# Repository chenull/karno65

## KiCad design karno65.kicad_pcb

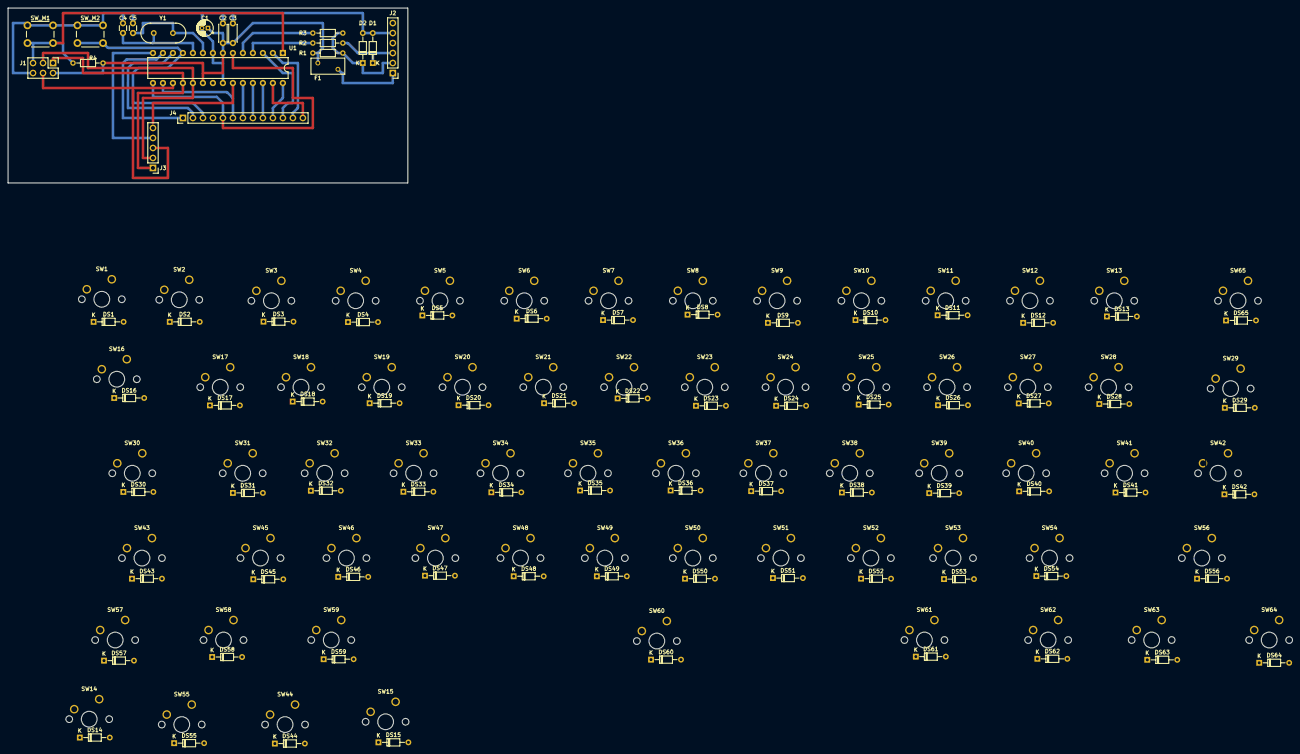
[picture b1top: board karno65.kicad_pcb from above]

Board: 2 copper layers, 101.6 x 44.5 mm, 156 parts (0 on the bottom side), 93 nets.

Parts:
C1: 10u; CP_Radial_D4.0mm_P1.50mm
C2, C3: 100n; C_Disc_D4.3mm_W1.9mm_P5.00mm
C4, C5: 20p; C_Disc_D3.0mm_W1.6mm_P2.50mm
D1, D2: 3.6V; D_DO-34_SOD68_P7.62mm_Horizontal
DS1, DS2, DS3, DS4, DS5, DS6, DS7, DS8, DS9, DS10, DS11, DS12, DS13, DS14, DS15, DS16, DS17, DS18, DS19, DS20, DS21, DS22, DS23, DS24, DS25, DS26, DS27, DS28, DS29, DS30, DS31, DS32, DS33, DS34, DS35, DS36, DS37, DS38, DS39, DS40, DS41, DS42, DS43, DS44, DS45, DS46, DS47, DS48, DS49, DS50, DS51, DS52, DS53, DS54, DS55, DS56, DS57, DS58, DS59, DS60, DS61, DS62, DS63, DS64, DS65: 1N4148; D_DO-34_SOD68_P7.62mm_Horizontal
F1: 100mA; Fuse_BelFuse_0ZRE0005FF_L8.3mm_W3.8mm
J1: AVR_ISP_6; PinHeader_2x03_P2.54mm_Vertical
J2: USB_OTG; PinHeader_1x06_P2.54mm_Vertical
J3: ROWS; PinHeader_1x05_P2.54mm_Vertical
J4: COLS; PinHeader_1x13_P2.54mm_Vertical
R1: 1.5k; R_Axial_DIN0204_L3.6mm_D1.6mm_P7.62mm_Horizontal
R2, R3: 75R; R_Axial_DIN0204_L3.6mm_D1.6mm_P7.62mm_Horizontal
R4: 10k; R_Axial_DIN0204_L3.6mm_D1.6mm_P7.62mm_Horizontal
STAB1, STAB2, STAB3, STAB4, STAB5, STAB6: 2U; MX_Stabilizer_Cutout-2u
SW1: GRV; SW_Cherry_MX1A_1.00u_PCB
SW2: 1; SW_Cherry_MX1A_1.00u_PCB
SW3: 2; SW_Cherry_MX1A_1.00u_PCB
SW4: 3; SW_Cherry_MX1A_1.00u_PCB
SW5: 4; SW_Cherry_MX1A_1.00u_PCB
SW6: 5; SW_Cherry_MX1A_1.00u_PCB
SW7: 6; SW_Cherry_MX1A_1.00u_PCB
SW8: 7; SW_Cherry_MX1A_1.00u_PCB
SW9: 8; SW_Cherry_MX1A_1.00u_PCB
SW10: 9; SW_Cherry_MX1A_1.00u_PCB
SW11: 0; SW_Cherry_MX1A_1.00u_PCB
SW12: MINS; SW_Cherry_MX1A_1.00u_PCB
SW13: EQL; SW_Cherry_MX1A_1.00u_PCB
SW14, SW15, SW44, SW55: SW_Push; SW_Cherry_MX1A_1.00u_PCB
SW16: TAB; SW_Cherry_MX1A_1.50u_PCB
SW17: Q; SW_Cherry_MX1A_1.00u_PCB
SW18: W; SW_Cherry_MX1A_1.00u_PCB
SW19: E; SW_Cherry_MX1A_1.00u_PCB
SW20: R; SW_Cherry_MX1A_1.00u_PCB
SW21: T; SW_Cherry_MX1A_1.00u_PCB
SW22: Y; SW_Cherry_MX1A_1.00u_PCB
SW23: U; SW_Cherry_MX1A_1.00u_PCB
SW24: I; SW_Cherry_MX1A_1.00u_PCB
SW25: O; SW_Cherry_MX1A_1.00u_PCB
SW26: P; SW_Cherry_MX1A_1.00u_PCB
SW27: LBRC; SW_Cherry_MX1A_1.00u_PCB
SW28: RBRC; SW_Cherry_MX1A_1.00u_PCB
SW29: BSLS; SW_Cherry_MX1A_1.50u_PCB
SW30: CAPS; SW_Cherry_MX1A_1.75u_PCB
SW31: A; SW_Cherry_MX1A_1.00u_PCB
SW32: S; SW_Cherry_MX1A_1.00u_PCB
SW33: D; SW_Cherry_MX1A_1.00u_PCB
SW34: F; SW_Cherry_MX1A_1.00u_PCB
SW35: G; SW_Cherry_MX1A_1.00u_PCB
SW36: H; SW_Cherry_MX1A_1.00u_PCB
SW37: J; SW_Cherry_MX1A_1.00u_PCB
SW38: K; SW_Cherry_MX1A_1.00u_PCB
SW39: L; SW_Cherry_MX1A_1.00u_PCB
SW40: SCLN; SW_Cherry_MX1A_1.00u_PCB
SW41: QUOT; SW_Cherry_MX1A_1.00u_PCB
SW42: ENT; SW_Cherry_MX1A_1.00u_PCB
SW43: LSFT; SW_Cherry_MX1A_1.00u_PCB
SW45: Z; SW_Cherry_MX1A_1.00u_PCB
SW46: X; SW_Cherry_MX1A_1.00u_PCB
SW47: C; SW_Cherry_MX1A_1.00u_PCB
SW48: V; SW_Cherry_MX1A_1.00u_PCB
SW49: B; SW_Cherry_MX1A_1.00u_PCB
SW50: N; SW_Cherry_MX1A_1.00u_PCB
SW51: M; SW_Cherry_MX1A_1.00u_PCB
SW52: COMM; SW_Cherry_MX1A_1.00u_PCB
SW53: DOT; SW_Cherry_MX1A_1.00u_PCB
SW54: SLSH; SW_Cherry_MX1A_1.00u_PCB
SW56: RSFT; SW_Cherry_MX1A_1.00u_PCB
SW57: LCTL; SW_Cherry_MX1A_1.25u_PCB
SW58: LGUI; SW_Cherry_MX1A_1.25u_PCB
SW59: LALT; SW_Cherry_MX1A_1.25u_PCB
SW60: SPC; SW_Cherry_MX1A_1.00u_PCB
SW61: RALT; SW_Cherry_MX1A_1.25u_PCB
SW62: RGUI; SW_Cherry_MX1A_1.25u_PCB
SW63: APP; SW_Cherry_MX1A_1.25u_PCB
SW64: RCTL; SW_Cherry_MX1A_1.25u_PCB
SW65: BSPC; SW_Cherry_MX1A_1.00u_PCB
SW_M1: RESET; SW_PUSH_6mm
SW_M2: BOOT; SW_PUSH_6mm
U1: ATmega328-PU; DIP-28_W7.62mm
Y1: 16Mhz; Crystal_HC49-4H_Vertical

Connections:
+5V: C1.1, C2.1, C3.1, F1.1, J1.2, R1.1, R4.1, U1.7, U1.20
/COL0: J4.1, SW1.1, SW14.1, SW27.1, SW40.1, SW53.1, U1.13
/COL1: J4.2, SW2.1, SW15.1, SW28.1, SW41.1, SW54.1, U1.12
/COL2: J4.3, SW3.1, SW16.1, SW29.1, SW42.1, SW55.1, SW_M2.1, U1.11
/COL3: J4.4, SW4.1, SW17.1, SW30.1, SW43.1, SW56.1
/COL4: J4.5, SW5.1, SW18.1, SW31.1, SW44.1, SW57.1, U1.6, U1.15
/COL5: J4.6, SW6.1, SW19.1, SW32.1, SW45.1, SW58.1, U1.16
/COL6: J4.7, SW7.1, SW20.1, SW33.1, SW46.1, SW59.1, U1.24
/COL7: J4.8, SW8.1, SW21.1, SW34.1, SW47.1, SW60.1, U1.25
/COL8: J4.9, SW9.1, SW22.1, SW35.1, SW48.1, SW61.1, U1.26
/COL9: J4.10, SW10.1, SW23.1, SW36.1, SW49.1, SW62.1, U1.28
/COL10: J4.11, SW11.1, SW24.1, SW37.1, SW50.1, SW63.1, U1.3
/COL11: J4.12, SW12.1, SW25.1, SW38.1, SW51.1, SW64.1, U1.2
/COL12: J4.13, SW13.1, SW26.1, SW39.1, SW52.1, SW65.1, U1.27
/RESET: J1.5, R4.2, SW_M1.1, U1.1
/ROW0: DS1.1, DS2.1, DS3.1, DS4.1, DS5.1, DS6.1, DS7.1, DS8.1, DS9.1, DS10.1, DS11.1, DS12.1, DS13.1, J1.1, J3.1, U1.18
/ROW1: DS14.1, DS15.1, DS16.1, DS17.1, DS18.1, DS19.1, DS20.1, DS21.1, DS22.1, DS23.1, DS24.1, DS25.1, DS26.1, J1.3, J3.2, U1.19
/ROW2: DS27.1, DS28.1, DS29.1, DS30.1, DS31.1, DS32.1, DS33.1, DS34.1, DS35.1, DS36.1, DS37.1, DS38.1, DS39.1, J1.4, J3.3, U1.17
/ROW3: DS40.1, DS41.1, DS42.1, DS43.1, DS44.1, DS45.1, DS46.1, DS47.1, DS48.1, DS49.1, DS50.1, DS51.1, DS52.1, J3.4, U1.14
/ROW4: DS53.1, DS54.1, DS55.1, DS56.1, DS57.1, DS58.1, DS59.1, DS60.1, DS61.1, DS62.1, DS63.1, DS64.1, DS65.1, J3.5, U1.23
/USB_D+: R2.1, U1.4
/USB_D-: R3.1, U1.5
GND: C1.2, C2.2, C3.2, C4.2, C5.2, D1.2, D2.2, J1.6, J2.5, SW_M1.2, SW_M2.2, U1.8, U1.22
unnamed: C4.1, U1.10, Y1.2
unnamed: C5.1, U1.9, Y1.1
unnamed: D1.1, J2.3, R2.2
unnamed: D2.1, J2.2, R1.2, R3.2
unnamed: DS1.2, SW1.2
unnamed: DS2.2, SW2.2
unnamed: DS3.2, SW3.2
unnamed: DS4.2, SW4.2
unnamed: DS5.2, SW5.2
unnamed: DS6.2, SW6.2
unnamed: DS7.2, SW7.2
unnamed: DS8.2, SW8.2
unnamed: DS9.2, SW9.2
unnamed: DS10.2, SW10.2
unnamed: DS11.2, SW11.2
unnamed: DS12.2, SW12.2
unnamed: DS13.2, SW13.2
unnamed: DS14.2, SW14.2
unnamed: DS15.2, SW15.2
unnamed: DS16.2, SW16.2
unnamed: DS17.2, SW17.2
unnamed: DS18.2, SW18.2
unnamed: DS19.2, SW19.2
unnamed: DS20.2, SW20.2
unnamed: DS21.2, SW21.2
unnamed: DS22.2, SW22.2
unnamed: DS23.2, SW23.2
unnamed: DS24.2, SW24.2
unnamed: DS25.2, SW25.2
unnamed: DS26.2, SW26.2
unnamed: DS27.2, SW27.2
unnamed: DS28.2, SW28.2
unnamed: DS29.2, SW29.2
unnamed: DS30.2, SW30.2
unnamed: DS31.2, SW31.2
unnamed: DS32.2, SW32.2
unnamed: DS33.2, SW33.2
unnamed: DS34.2, SW34.2
unnamed: DS35.2, SW35.2
unnamed: DS36.2, SW36.2
unnamed: DS37.2, SW37.2
unnamed: DS38.2, SW38.2
unnamed: DS39.2, SW39.2
unnamed: DS40.2, SW40.2
unnamed: DS41.2, SW41.2
unnamed: DS42.2, SW42.2
unnamed: DS43.2, SW43.2
unnamed: DS44.2, SW44.2
unnamed: DS45.2, SW45.2
unnamed: DS46.2, SW46.2
unnamed: DS47.2, SW47.2
unnamed: DS48.2, SW48.2
unnamed: DS49.2, SW49.2
unnamed: DS50.2, SW50.2
unnamed: DS51.2, SW51.2
unnamed: DS52.2, SW52.2
unnamed: DS53.2, SW53.2
unnamed: DS54.2, SW54.2
unnamed: DS55.2, SW55.2
unnamed: DS56.2, SW56.2
unnamed: DS57.2, SW57.2
unnamed: DS58.2, SW58.2
unnamed: DS59.2, SW59.2
unnamed: DS60.2, SW60.2
unnamed: DS61.2, SW61.2
unnamed: DS62.2, SW62.2
unnamed: DS63.2, SW63.2
unnamed: DS64.2, SW64.2
unnamed: DS65.2, SW65.2
unnamed: F1.2, J2.1

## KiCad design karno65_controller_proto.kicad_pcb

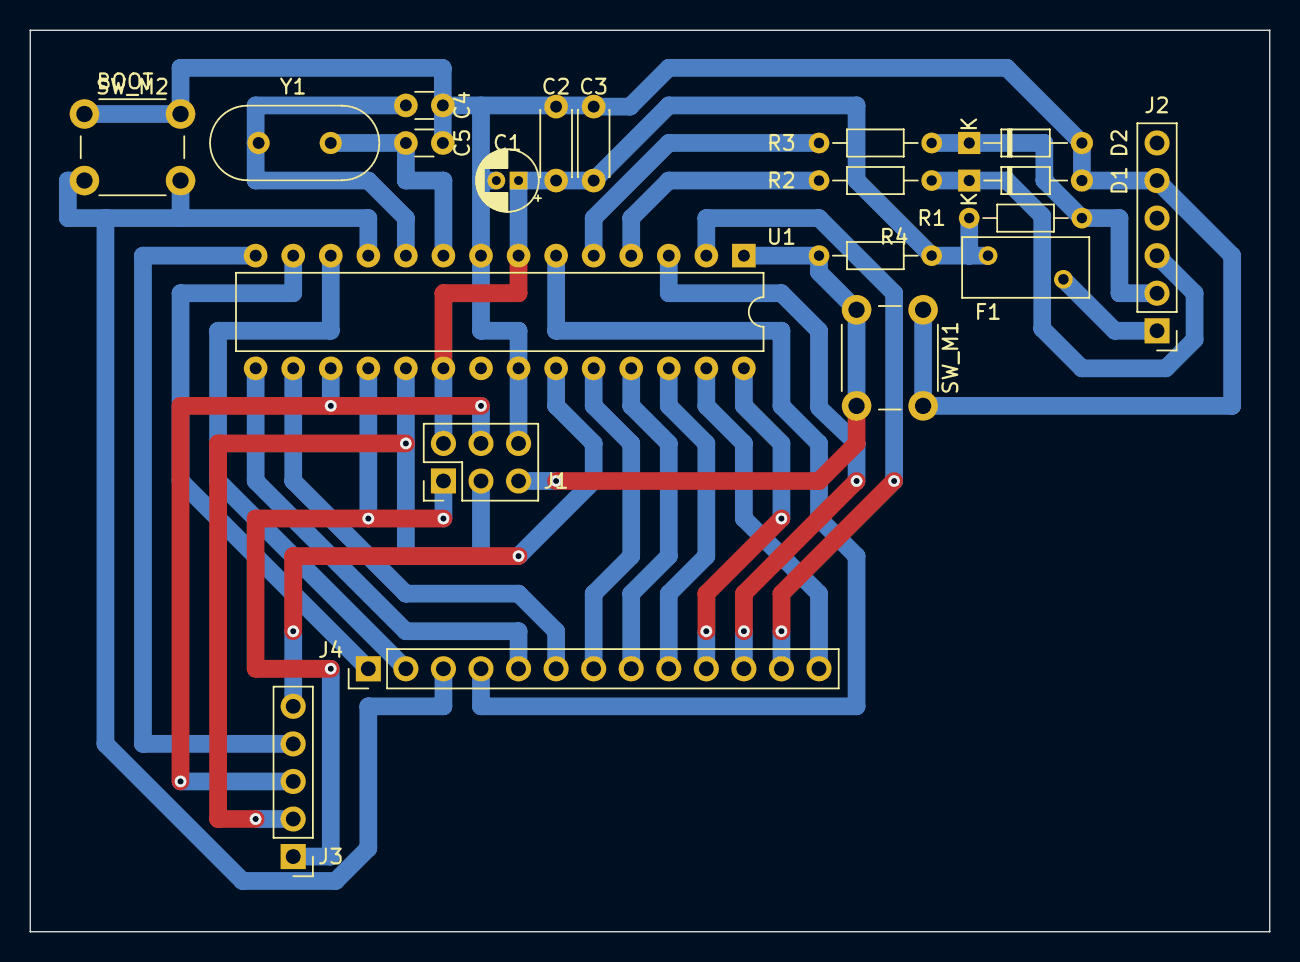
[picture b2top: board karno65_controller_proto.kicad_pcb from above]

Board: 2 copper layers, 83.8 x 61.0 mm, 20 parts (0 on the bottom side), 28 nets.

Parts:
C1: 10u; CP_Radial_D4.0mm_P1.50mm
C2, C3: 100n; C_Disc_D4.3mm_W1.9mm_P5.00mm
C4, C5: 20p; C_Disc_D3.0mm_W1.6mm_P2.50mm
D1, D2: 3.6V; D_DO-34_SOD68_P7.62mm_Horizontal
F1: 100mA; Fuse_BelFuse_0ZRE0005FF_L8.3mm_W3.8mm
J1: AVR_ISP_6; PinHeader_2x03_P2.54mm_Vertical
J2: USB_OTG; PinHeader_1x06_P2.54mm_Vertical
J3: ROWS; PinHeader_1x05_P2.54mm_Vertical
J4: COLS; PinHeader_1x13_P2.54mm_Vertical
R1: 1.5k; R_Axial_DIN0204_L3.6mm_D1.6mm_P7.62mm_Horizontal
R2, R3: 75R; R_Axial_DIN0204_L3.6mm_D1.6mm_P7.62mm_Horizontal
R4: 10k; R_Axial_DIN0204_L3.6mm_D1.6mm_P7.62mm_Horizontal
SW_M1: RESET; SW_PUSH_6mm
SW_M2: BOOT; SW_PUSH_6mm
U1: ATmega328-PU; DIP-28_W7.62mm
Y1: 16Mhz; Crystal_HC49-4H_Vertical

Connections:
+5V: C1.1, C2.1, C3.1, F1.1, J1.2, R1.1, R4.1, U1.7, U1.20
/COL0: J4.1, U1.13
/COL1: J4.2, U1.12
/COL2: J4.3, SW_M2.1, U1.11
/COL3: J4.4, U1.6
/COL4: J4.5, U1.15
/COL5: J4.6, U1.16
/COL6: J4.7, U1.24
/COL7: J4.8, U1.25
/COL8: J4.9, U1.26
/COL9: J4.10, U1.28
/COL10: J4.11, U1.3
/COL11: J4.12, U1.2
/COL12: J4.13, U1.27
/RESET: J1.5, R4.2, SW_M1.1, U1.1
/ROW0: J1.1, J3.1, U1.18
/ROW1: J1.3, J3.2, U1.19
/ROW2: J1.4, J3.3, U1.17
/ROW3: J3.4, U1.14
/ROW4: J3.5, U1.23
/USB_D+: R2.1, U1.4
/USB_D-: R3.1, U1.5
GND: C1.2, C2.2, C3.2, C4.2, C5.2, D1.2, D2.2, J1.6, J2.5, SW_M1.2, SW_M2.2, U1.8, U1.22
unnamed: C4.1, U1.10, Y1.2
unnamed: C5.1, U1.9, Y1.1
unnamed: D1.1, J2.3, R2.2
unnamed: D2.1, J2.2, R1.2, R3.2
unnamed: F1.2, J2.1

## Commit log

2020-05-30 init
2020-05-31 proto
2020-06-01 fix grid
2020-06-01 one side
2020-06-02 fix boot sw
2020-06-02 via 0.9
2020-06-03 caseplate
2020-06-03 reversed t caseplate
